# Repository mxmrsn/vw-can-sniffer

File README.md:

# VW CAN Sniffer

Hardware-agnostic CAN bus sniffer focused on MK7.5 VW GTI, starting with Teensy 4.0 and a UART stream protocol suitable for an ESP32 Wi‑Fi dashboard.

## Scope
- Teensy 4.0 CAN capture
- UART framing protocol for streaming frames to a Wi‑Fi module
- Future STM32H7 custom board

## Current Contents
- `firmware/teensy/teensy_uart_streamer.ino`
- `firmware/teensy/teensy_can_simulator.ino`
- `docs/uart_protocol.md`
- `firmware/esp32/esp32_uart_gateway.ino`

## Hardware (Initial Setup)
- Teensy 4.0
- CAN transceiver (TJA1051T/3 recommended)
- ESP32 module (UART bridge for Wi‑Fi)

### Basic Wiring (Teensy ↔ ESP32)
- `Teensy TX` → `ESP32 RX`
- `Teensy RX` ← `ESP32 TX`
- `GND` ↔ `GND`
- Optional: `Teensy pin 4` → `ESP32 EN` (reset control)
- Optional: `Teensy pin 5` → `ESP32 RST` (soft reset)

### CAN Transceiver (Optional Control)
- Optional: `Teensy pin 20` → TJA1051 `S` (silent/listen‑only control)

### Output Mode + LEDs
- Mode button: `pin 8` (toggle UART/Wi‑Fi vs USB)
- Select button: `pin 9` (toggle CAN silent)
- LEDs: CAN heartbeat `pin 14`, Wi‑Fi active `pin 15`, USB active `pin 16`, silent indicator `pin 21`

## Firmware Notes
- Default UART: `Serial1` @ `921600`
- Default CAN speed: `500000`
- CAN IDs encode extended frames with bit31 set

## System Block Diagram
```
                 CANH/CANL
   ┌──────────────────────────────────────────┐
   │              Bench / Vehicle             │
   └──────────────────────────────────────────┘
                    │
                    │
              ┌──────────┐        UART (3.3V)
              │ TJA1051  │<-------------------------┐
              └──────────┘                          │
                    │ TXD/RXD                       │
                    │                               │
            ┌────────────────┐                      │
            │ Teensy 4.0     │                      │
            │ CAN1 (pins 22/23)                     │
            │ UART -> ESP32  │----------------------┘
            └────────────────┘
                       │ Wi-Fi
                       │
                 ┌──────────┐
                 │  ESP32   │
                 │ Web UI   │
                 └──────────┘
                       │
                       │ HTTP/WS
                       ▼
                 ┌──────────┐
                 │ Browser  │
                 └──────────┘
```

## Wiring Overview (ASCII)
```
Teensy 4.0                          TJA1051T/3                 CAN Bus
-----------                          ----------                 -------
CTX1 (pin 22) ---------------------> TXD
CRX1 (pin 23) <--------------------- RXD
pin 20 ----------------------------> S (silent)
3V3 -------------------------------> VIO
5V  -------------------------------> VCC
GND -------------------------------> GND ---------------------- GND
                                   CANH ---------------------- CANH
                                   CANL ---------------------- CANL

Teensy 4.0                          ESP32 (UART)               Wi-Fi
-----------                          -----------               -----
TX1 (pin 1) ----------------------> RX
RX1 (pin 0) <---------------------- TX
GND ------------------------------> GND                         ~~~

LEDs / Buttons (Teensy 4.0)
LED CAN (pin 14), LED Wi-Fi (pin 15), LED USB (pin 16), LED Silent (pin 21)
Mode button (pin 8), Select button (pin 9)
```

### Test Mode
Enable synthetic frames for bench testing:

```
#define TEST_MODE 1
#define TEST_RATE_HZ 50
```

## Protocol
See `docs/uart_protocol.md` for the UART framing spec.

## USB Capture
Use `tools/usb_dump.py` to read the framed stream from USB and emit CSV.
Requires `pyserial`.

## PCB Docs
See `pcb-teensy-esp32/teensy-esp32-can-sniffer/docs/README.md` for schematic, layout, and 3D captures.

## Next Steps
- ESP32 firmware to host a WebSocket dashboard
- Basic browser UI for live frame display
- STM32H7 hardware plan

## PlatformIO (ESP32)
If you prefer automation, PlatformIO can build and upload the ESP32 firmware and SPIFFS assets.
See `platformio.ini` and `tools/upload_spiffs.sh`.

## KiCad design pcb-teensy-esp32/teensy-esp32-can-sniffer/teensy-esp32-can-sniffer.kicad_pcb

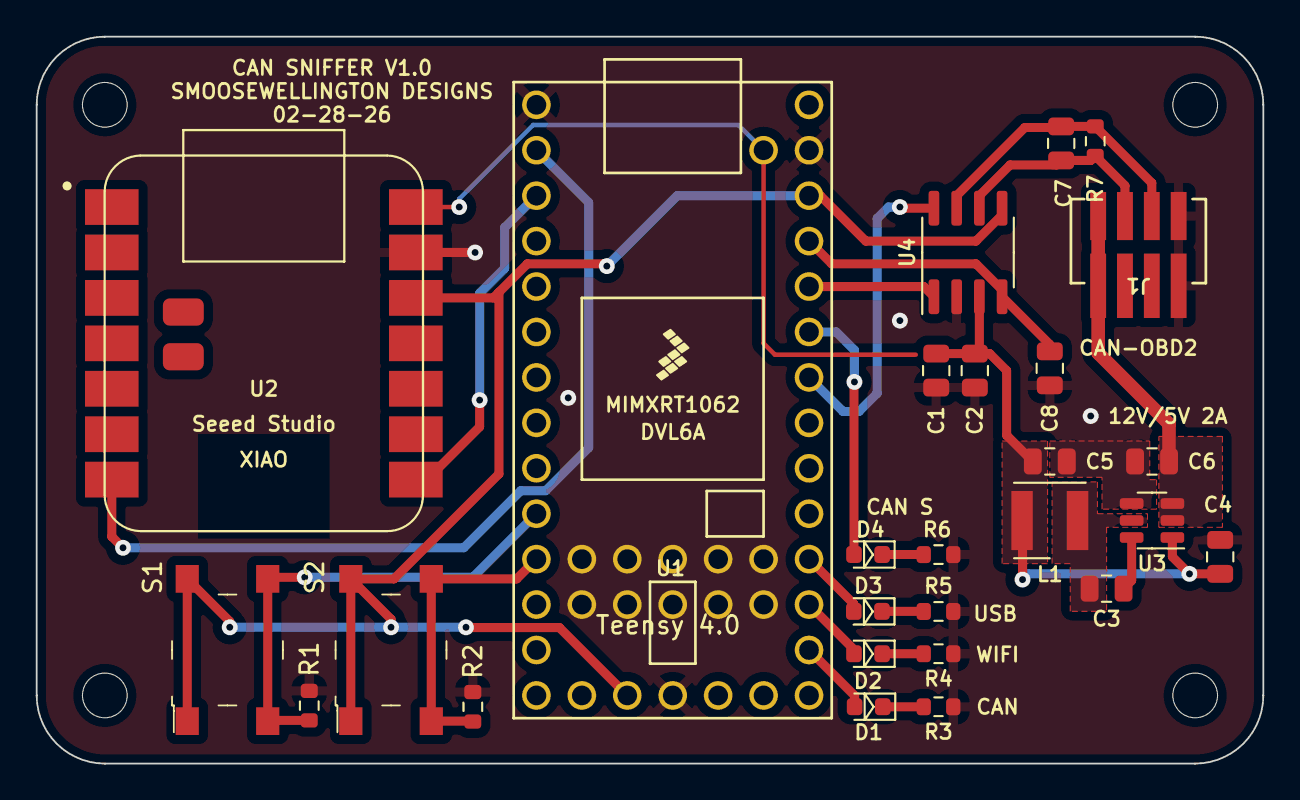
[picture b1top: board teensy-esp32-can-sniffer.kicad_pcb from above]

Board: 2 copper layers, 68.6 x 40.6 mm, 31 parts (0 on the bottom side), 23 nets.

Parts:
C1, C3: 100n; C_0805_2012Metric
C2: 47u; C_0805_2012Metric
C4, C5: 22u; C_0805_2012Metric
C6: 10u; C_0805_2012Metric
C7: 100p; C_0805_2012Metric
C8: 15p; C_0805_2012Metric
D1, D2, D3, D4: LED; LED_0603_1608Metric
H1, H2, H3, H4: MountingHole; MountingHole_2.5mm
J1: Conn_01x04; CONN_874370231-SD_04_MOL
L1: 4.7u; L_Wurth_WE-LQSH-4020
R1, R2: 10k; R_0603_1608Metric
R3, R4, R5, R6: 330; R_0603_1608Metric
R7: 120; R_0603_1608Metric
S1, S2: PTS645SM43SMTR92_LFS; Switch_Tactile_SMD_6x6mm_PTS645
U1: Teensy4.0; Teensy40
U2: Seeed_Studio_XIAO_ESP32S3; XIAO-ESP32S3
U3: AP63205WU; TSOT-23-6
U4: TJA1051T-3; SOIC-8_3.9x4.9mm_P1.27mm

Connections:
+3V3: S1.1, S1.2, S2.1, S2.2, U1.16 (3V3), U1.31 (3V3), U2.12 (3V3), U4.5 (VIO)
+5V: C1.1, C2.1, C4.1, C5.1, L1.2, U1.33 (VIN), U1.34 (VUSB), U2.14 (5V), U3.1 (FB), U4.3 (VCC)
+12V: C6.1, J1.1, U3.2 (EN), U3.3 (IN)
/BUTTON_MODE: R1.1, S1.3, S1.4, U1.10 (8_TX2_IN1)
/BUTTON_SELECT: R2.1, S2.3, S2.4, U1.11 (9_OUT1C)
/CAN_HEARTBEAT: D1.2 (A), U1.21 (14_A0_TX3_SPDIF_OUT)
/CAN_SILENT_STATUS: D4.2 (A), U1.28 (21_A7_RX5_BCLK1)
/SW: C3.2, L1.1, U3.5 (SW)
/USB_HEARTBEAT: D3.2 (A), U1.23 (16_A2_RX4_SCL1)
/WIFI_HEARTBEAT: D2.2 (A), U1.22 (15_A1_RX3_SPDIF_IN)
CAN_H: C7.1, J1.3, R7.1, U4.7 (CANH)
CAN_L: C7.2, J1.2, R7.2, U4.6 (CANL)
CAN_SILENT: U1.27 (20_A6_TX5_LRCLK1), U4.8 (S)
CRX: C8.1, U1.30 (23_A9_CRX1_MCLK1), U4.4 (RXD)
CTX: U1.29 (22_A8_CTX1), U4.1 (TXD)
ESP_UART_RX: U1.3 (1_TX1_CTX2_MISO1), U2.8 (PB09_A7_D7_RX)
ESP_UART_TX: U1.2 (0_RX1_CRX2_CS1), U2.7 (PB08_A6_D6_TX)
GND: C1.2, C2.2, C4.2, C5.2, C6.2, C8.2, J1.4, R1.2, R2.2, R3.2, R4.2, R5.2, R6.2, U1.1 (GND), U1.17 (GND), U1.32 (GND), U2.13 (GND), U3.4 (GND), U4.2 (GND)
unnamed: C3.1, U3.6 (BST)
unnamed: D1.1 (K), R3.1
unnamed: D2.1 (K), R4.1
unnamed: D3.1 (K), R5.1
unnamed: D4.1 (K), R6.1

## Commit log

2026-02-28 Initial CAN sniffer scaffolding
2026-02-28 Add README and Teensy setup guide
2026-02-28 Serve ESP32 UI from SPIFFS
2026-02-28 Add PlatformIO SPIFFS upload script
2026-02-28 Add ESP32 upload scripts
2026-02-28 Add ESP32 heartbeat and stats
2026-02-28 Recommend TJA1051 transceiver
2026-02-28 Add Teensy CAN simulator
2026-02-28 Add TJA1051 wiring notes
2026-02-28 Document Teensy 4.1 CAN pins
2026-02-28 Add CAN1 wiring table
2026-02-28 Add system block diagram
2026-02-28 Improve dashboard with filters and stats
2026-02-28 Add Teensy-controlled ESP32 reset
2026-02-28 Add Teensy control of ESP32 RST
2026-02-28 Pulse ESP32 RST on boot
2026-02-28 Add CAN silent mode control
2026-02-28 Add Teensy heartbeat LED
2026-03-01 Add gitignore for PCB artifacts
2026-03-01 Ignore and untrack KiCad backups
2026-03-01 Add Teensy output mode switch and LEDs
2026-03-01 Add PCB doc with screenshots
2026-03-01 Link PCB docs in README
2026-03-01 Blink Wi-Fi LED in UART mode
2026-03-01 Add Teensy pins header and status frames
2026-03-01 Add status frames to dashboard and USB dump tool
2026-03-01 Document USB capture and stats
2026-03-01 Add wiring overview diagram
2026-03-01 Add UI control commands and state frames
2026-03-01 Add UI preview script
2026-03-01 Add mock data mode for UI preview
2026-03-01 Add UI labels and update PCB assets
2026-03-01 Enhance UI labeling
2026-03-01 Relocate labels card
2026-03-01 Reflow dashboard columns
2026-03-01 Fix labels render bug
2026-03-01 Fix filter interaction
2026-03-01 Make filters re-render immediately
2026-03-01 Add inline chart
2026-03-01 Add selectable plot targets
2026-03-01 Fix chart declaration
2026-03-01 Polish chart dropdowns
2026-03-01 Stabilize chart label selection
2026-03-01 Clear chart on target change
2026-03-01 Reset other dropdown on selection
2026-03-01 Add axis and grid to chart
2026-03-01 Add byte dropdown for plot
2026-03-01 Make chart collapsible
2026-03-01 Make chart hide/show
